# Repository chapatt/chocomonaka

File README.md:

# choco monaka

Fighting game controller

* [abalog.io](https://abalog.io)
* integrated RP2040
* compatible with [GP2040-CE firmware](https://gp2040-ce.info/)
* 18 face buttons
* Kailh Choc hotswap switches (v1 and v2 compatible)
* USB-C
* two slider switches (for e.g. tournament lockout, SOCD)
* USB-A for auth passthrough
* 0.96-in. OLED
* 254 x 127 x 17mm

PCB artwork:

v0.1.0 prototype front:

v0.1.0 prototype back:

v0.1.0 prototype edge:

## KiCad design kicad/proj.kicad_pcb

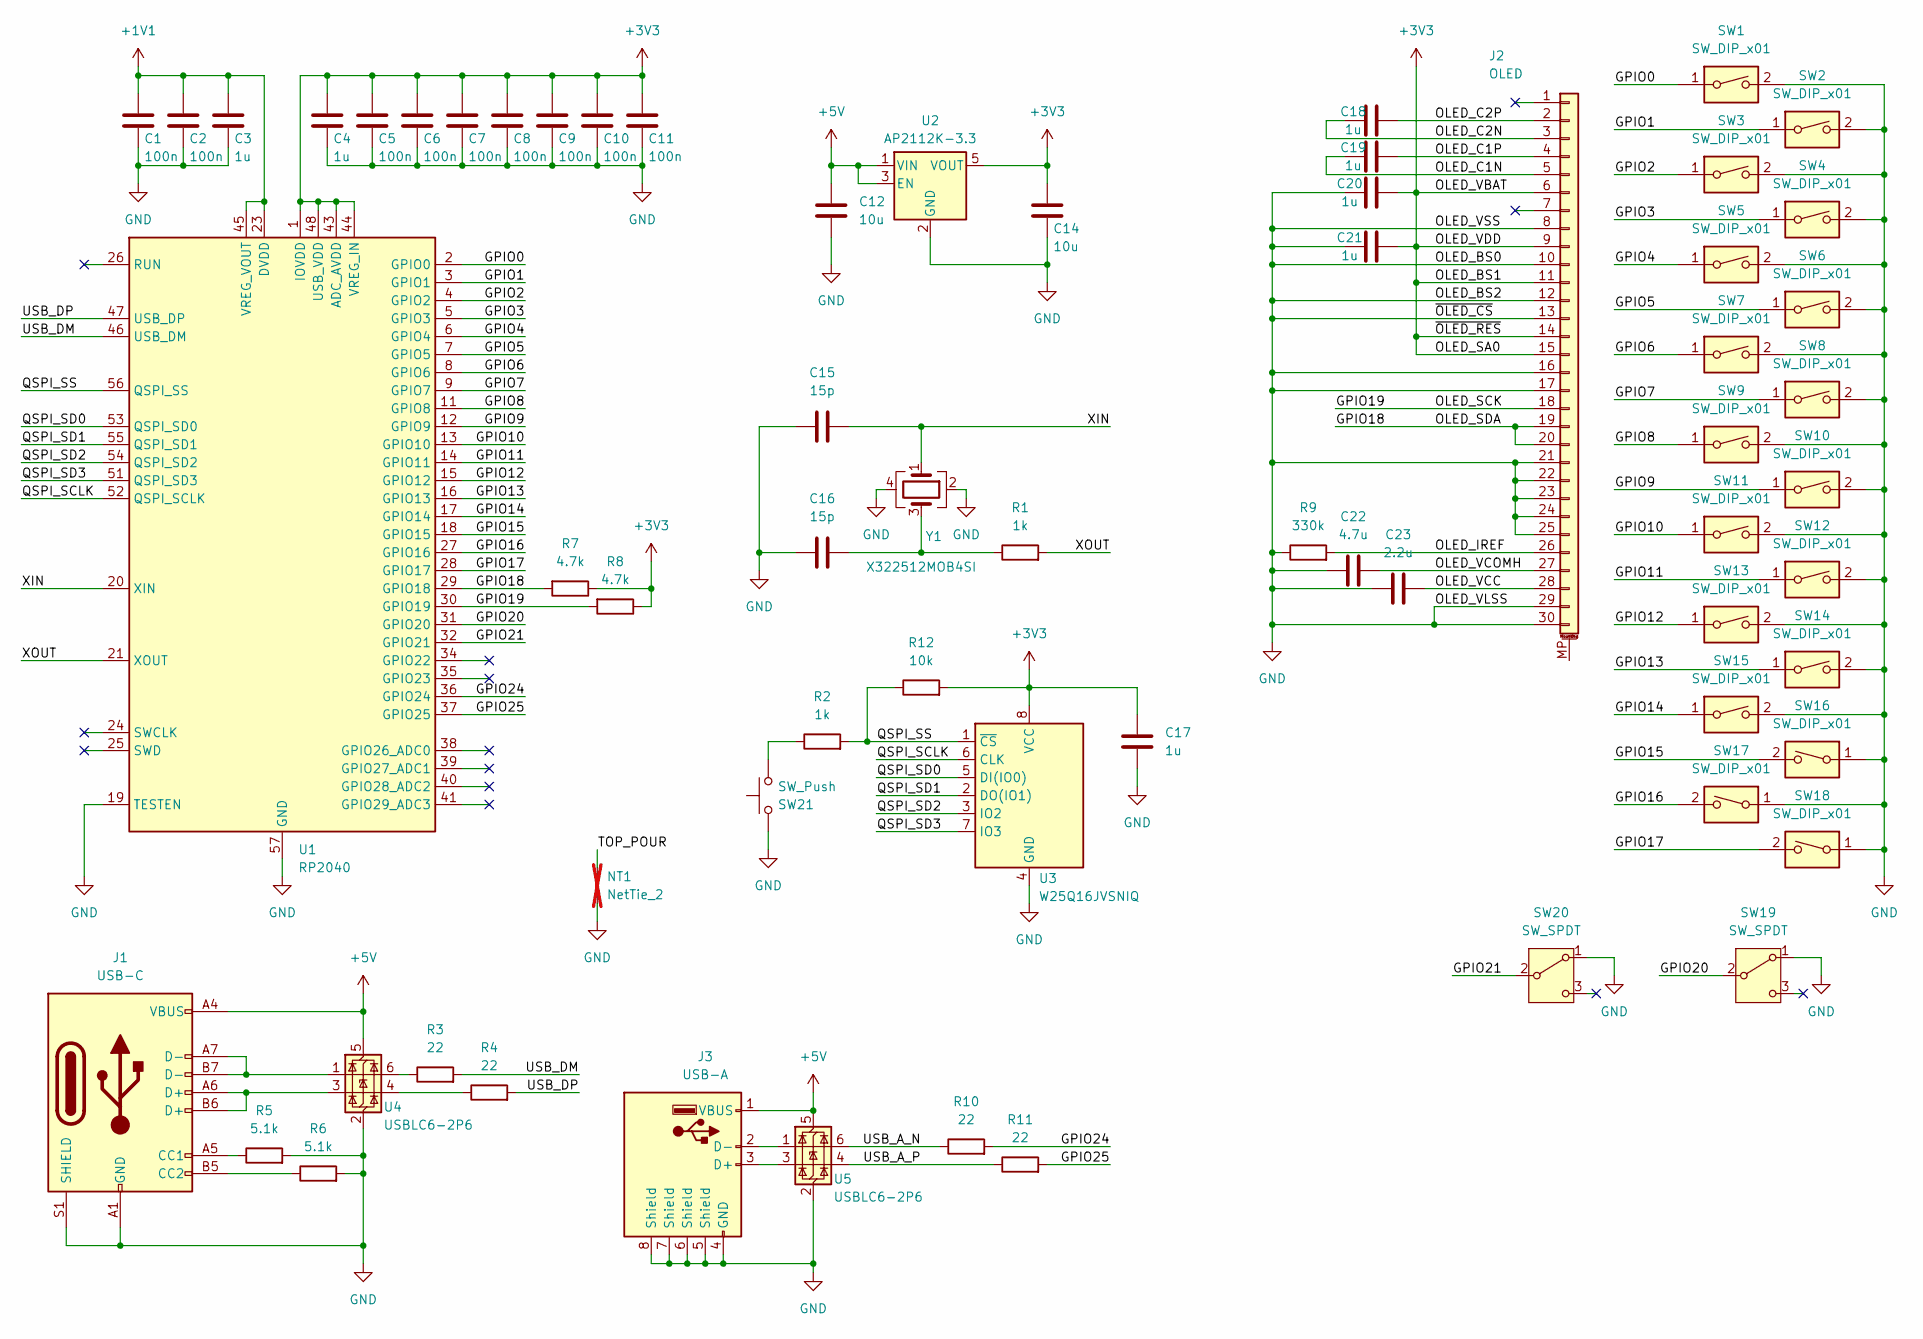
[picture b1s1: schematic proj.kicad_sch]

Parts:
C1, C2, C5, C6, C7, C8, C9, C10, C11: 100n; C_0402_1005Metric; LCSC C1525
C3, C4, C17, C18, C19, C20, C21: 1u; C_0402_1005Metric; LCSC C52923
C12, C14: 10u; C_0805_2012Metric; LCSC C15850
C15, C16: 15p; C_0402_1005Metric; LCSC C1548
C22: 4.7u; C_0805_2012Metric; LCSC C1779
C23: 2.2u; C_0805_2012Metric; LCSC C377773
J1: USB-C; USB_C_Receptacle_XKB_U262-16XN-4BVC11; LCSC C319148
J2: OLED; FPC-SMD_30P-P0.50_HDGC_0.5K-BS-30PWB; LCSC C2915410
J3: USB-A; USB-A-SMD_USB-M-21; LCSC C6331170
NT1: NetTie_2; NetTie-2_SMD_Pad0.5mm; not fitted
R1, R2: 1k; R_0402_1005Metric; LCSC C11702
R3, R4, R10, R11: 22; R_0402_1005Metric; LCSC C25092
R5, R6: 5.1k; R_0402_1005Metric; LCSC C25905
R7, R8: 4.7k; R_0402_1005Metric; LCSC C25900
R9: 330k; R_0402_1005Metric; LCSC C25104
R12: 10k; R_0402_1005Metric; LCSC C25744
SW1, SW2, SW3, SW4, SW5, SW6, SW7, SW8, SW9, SW10, SW11, SW12, SW13, SW14, SW15, SW16, SW17, SW18: SW_DIP_x01; SW_Hotswap_Kailh_Choc_V1V2; LCSC C5333465
SW19, SW20: SW_SPDT; SW-SMD_SS-1290; LCSC C589295
SW21: SW_Push; KEY-SMD_4P-L4.2-W3.2-P2.20-LS4.6; LCSC C470427
U1: RP2040; RP2040-QFN-56; LCSC C2040
U2: AP2112K-3.3; SOT-23-5; LCSC C51118
U3: W25Q16JVSNIQ; SOIC-8_3.9x4.9mm_P1.27mm; LCSC C2456211
U4, U5: USBLC6-2P6; SOT-666; LCSC C15999
Y1: X322512MOB4SI; Crystal_SMD_3225-4Pin_3.2x2.5mm; LCSC C70565

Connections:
+1V1: C1.1, C2.1, C3.1, U1.23 (DVDD), U1.45 (VREG_VOUT), U1.50 (DVDD)
+3V3: C4.1, C5.1, C6.1, C7.1, C8.1, C9.1, C10.1, C11.1, C14.1, C17.2, C20.2, C21.2, J2.6, J2.9, J2.11, J2.14, J2.15, R7.1, R8.1, R12.2, U1.1 (IOVDD), U1.10 (IOVDD), U1.22 (IOVDD), U1.33 (IOVDD), U1.42 (IOVDD), U1.43 (ADC_AVDD), U1.44 (VREG_IN), U1.48 (USB_VDD), U1.49 (IOVDD), U2.5 (VOUT), U3.8 (VCC)
+5V: C12.1, J1.A4 (VBUS), J1.A9 (VBUS), J1.B4 (VBUS), J1.B9 (VBUS), J3.1 (VBUS), U2.1 (VIN), U2.3 (EN), U4.5 (VBUS), U5.5 (VBUS)
/GPIO0: SW1.1, U1.2 (GPIO0)
/GPIO1: SW2.1, U1.3 (GPIO1)
/GPIO2: SW3.1, U1.4 (GPIO2)
/GPIO3: SW4.1, U1.5 (GPIO3)
/GPIO4: SW5.1, U1.6 (GPIO4)
/GPIO5: SW6.1, U1.7 (GPIO5)
/GPIO6: SW7.1, U1.8 (GPIO6)
/GPIO7: SW8.1, U1.9 (GPIO7)
/GPIO8: SW9.1, U1.11 (GPIO8)
/GPIO9: SW10.1, U1.12 (GPIO9)
/GPIO10: SW11.1, U1.13 (GPIO10)
/GPIO11: SW12.1, U1.14 (GPIO11)
/GPIO12: SW13.1, U1.15 (GPIO12)
/GPIO13: SW14.1, U1.16 (GPIO13)
/GPIO14: SW15.1, U1.17 (GPIO14)
/GPIO15: SW16.2, U1.18 (GPIO15)
/GPIO16: SW17.2, U1.27 (GPIO16)
/GPIO17: SW18.2, U1.28 (GPIO17)
/GPIO18: J2.19, J2.20, R7.2, U1.29 (GPIO18)
/GPIO19: J2.18, R8.2, U1.30 (GPIO19)
/GPIO20: SW19.2 (B), U1.31 (GPIO20)
/GPIO21: SW20.2 (B), U1.32 (GPIO21)
/GPIO24: R10.2, U1.36 (GPIO24)
/GPIO25: R11.2, U1.37 (GPIO25)
/OLED_C1N: C19.1, J2.5
/OLED_C1P: C19.2, J2.4
/OLED_C2N: C18.1, J2.3
/OLED_C2P: C18.2, J2.2
/OLED_IREF: J2.26, R9.2
/OLED_VCC: C23.2, J2.28
/OLED_VCOMH: C22.2, J2.27
/QSPI_SCLK: U1.52 (QSPI_SCLK), U3.6 (CLK)
/QSPI_SD0: U1.53 (QSPI_SD0), U3.5 (DI(IO0))
/QSPI_SD1: U1.55 (QSPI_SD1), U3.2 (DO(IO1))
/QSPI_SD2: U1.54 (QSPI_SD2), U3.3 (IO2)
/QSPI_SD3: U1.51 (QSPI_SD3), U3.7 (IO3)
/QSPI_SS: R2.2, R12.1, U1.56 (QSPI_SS), U3.1 (~CS)
/TOP_POUR: NT1.2
/USB_A_N: R10.1, U5.6 (I/O1)
/USB_A_P: R11.1, U5.4 (I/O2)
/USB_DM: R3.2, U1.46 (USB_DM)
/USB_DP: R4.2, U1.47 (USB_DP)
/XIN: C15.2, U1.20 (XIN), Y1.1
/XOUT: R1.2, U1.21 (XOUT)
GND: C1.2, C2.2, C3.2, C4.2, C5.2, C6.2, C7.2, C8.2, C9.2, C10.2, C11.2, C12.2, C14.2, C15.1, C16.1, C17.1, C20.1, C21.1, C22.1, C23.1, J1.A1 (GND), J1.A12 (GND), J1.B1 (GND), J1.B12 (GND), J1.S1 (SHIELD), J2.8, J2.10, J2.12, J2.13, J2.16, J2.17, J2.21, J2.22, J2.23, J2.24, J2.25, J2.29, J2.30, J3.4 (GND), J3.5 (Shield), J3.6 (Shield), J3.7 (Shield), J3.8 (Shield), NT1.1, R5.2, R6.2, R9.1, SW1.2, SW2.2, SW3.2, SW4.2, SW5.2, SW6.2, SW7.2, SW8.2, SW9.2, SW10.2, SW11.2, SW12.2, SW13.2, SW14.2, SW15.2, SW16.1, SW17.1, SW18.1, SW19.1 (A), SW20.1 (A), SW21.2, U1.19 (TESTEN), U1.57 (GND), U2.2 (GND), U3.4 (GND), U4.2 (GND), U5.2 (GND), Y1.2, Y1.4
unnamed: C16.2, R1.1, Y1.3
unnamed: J1.A5 (CC1), R5.1
unnamed: J1.B5 (CC2), R6.1
unnamed: J1.A6 (D+), J1.B6 (D+), U4.3 (I/O2)
unnamed: J1.A7 (D-), J1.B7 (D-), U4.1 (I/O1)
unnamed: J3.3 (D+), U5.3 (I/O2)
unnamed: J3.2 (D-), U5.1 (I/O1)
unnamed: R2.1, SW21.1
unnamed: R3.1, U4.6 (I/O1)
unnamed: R4.1, U4.4 (I/O2)

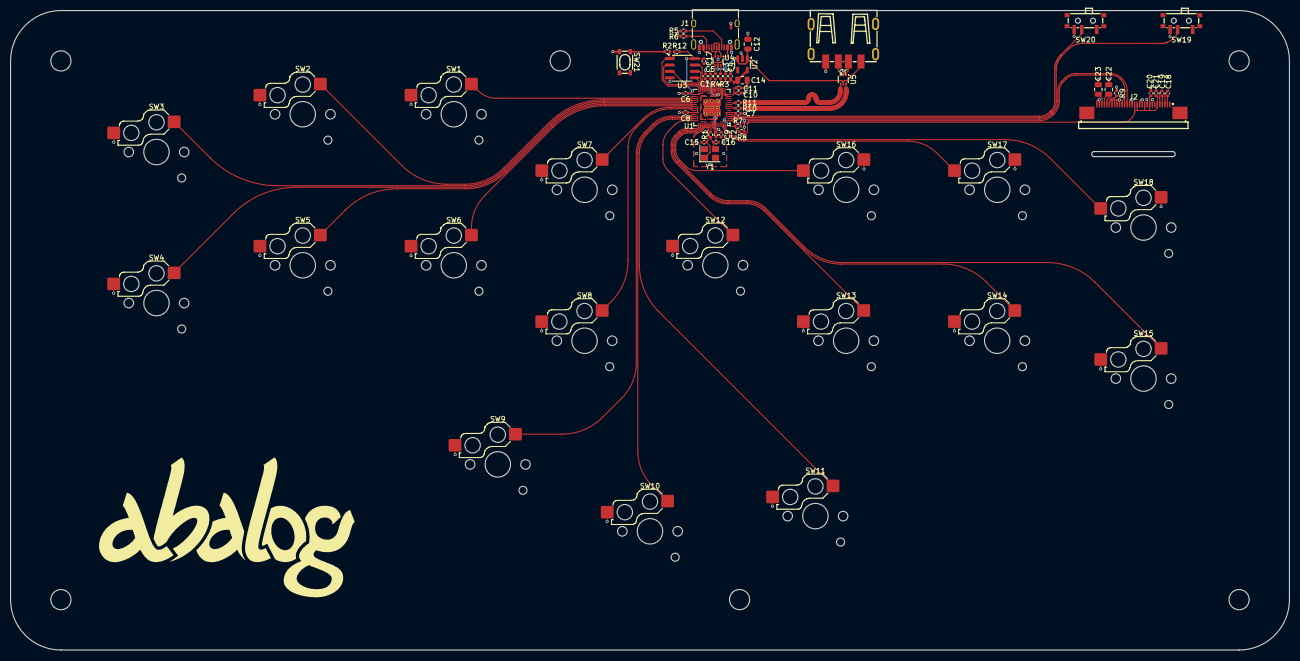
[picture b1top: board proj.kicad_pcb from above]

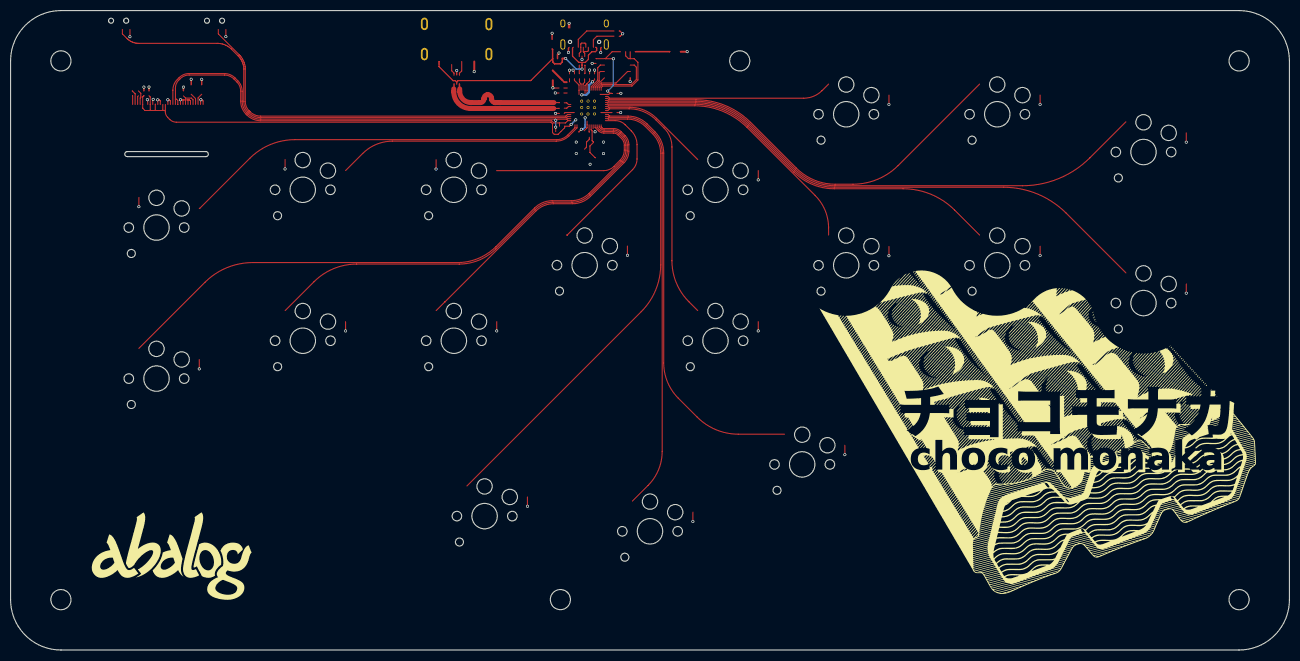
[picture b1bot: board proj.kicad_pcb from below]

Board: 2 copper layers, 254.0 x 127.0 mm, 65 parts (18 on the bottom side), 57 nets.

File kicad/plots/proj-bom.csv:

Comment,Designator,Footprint,LCSC
"100n","C1,C2,C5,C6,C7,C8,C9,C10,C11","Capacitor_SMD:C_0402_1005Metric","C1525"
"10u","C12,C14","Capacitor_SMD:C_0805_2012Metric","C15850"
"15p","C15,C16","Capacitor_SMD:C_0402_1005Metric","C1548"
"4.7u","C22","Capacitor_SMD:C_0805_2012Metric","C1779"
"2.2u","C23","Capacitor_SMD:C_0805_2012Metric","C377773"
"1u","C3,C4,C17,C18,C19,C20,C21","Capacitor_SMD:C_0402_1005Metric","C52923"
"USB-C","J1","proj:USB_C_Receptacle_XKB_U262-16XN-4BVC11","C319148"
"OLED","J2","proj:FPC-SMD_30P-P0.50_HDGC_0.5K-BS-30PWB","C2915410"
"USB-A","J3","proj:USB-A-SMD_USB-M-21","C42559"
"1k","R1,R2","Resistor_SMD:R_0402_1005Metric","C11702"
"10k","R12","Resistor_SMD:R_0402_1005Metric","C25744"
"22","R3,R4,R10,R11","Resistor_SMD:R_0402_1005Metric","C25092"
"5.1k","R5,R6","Resistor_SMD:R_0402_1005Metric","C25905"
"4.7k","R7,R8","Resistor_SMD:R_0402_1005Metric","C25900"
"330k","R9","Resistor_SMD:R_0402_1005Metric","C25104"
"SW_DIP_x01","SW1,SW2,SW3,SW4,SW5,SW6,SW7,SW8,SW9,SW10,SW11,SW12,SW13,SW14,SW15,SW16,SW17,SW18","proj:SW_Hotswap_Kailh_Choc_V1V2","C5333465"
"SW_SPDT","SW19,SW20","proj:SW-SMD_SS-1290","C589295"
"SW_Push","SW21","proj:KEY-SMD_4P-L4.2-W3.2-P2.20-LS4.6","C470427"
"RP2040","U1","proj:RP2040-QFN-56","C2040"
"AP2112K-3.3","U2","Package_TO_SOT_SMD:SOT-23-5","C51118"
"W25Q16JVSNIQ","U3","Package_SO:SOIC-8_3.9x4.9mm_P1.27mm","C2456211"
"USBLC6-2P6","U4,U5","Package_TO_SOT_SMD:SOT-666","C15999"
"X322512MOB4SI","Y1","Crystal:Crystal_SMD_3225-4Pin_3.2x2.5mm","C70565"

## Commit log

2024-03-29 fillet trace corners
2024-03-29 remove unnecessary xtal guard ring keepout
2024-03-30 add artwork to board
2024-03-30 adapt for LCSC part numbers
2024-03-31 remove redundant 3dmodels dir
2024-03-31 replace USB-A with top mount part
2024-03-31 add fabrication outputs
2024-04-01 add 3d renders of board
2024-04-15 add initial laser cut files
2024-04-16 add acrylic layouts
2024-04-16 add reset pinhole
2024-05-03 feat: add firmware
2024-05-03 feat: remove large file
2024-05-03 docs: add readme
